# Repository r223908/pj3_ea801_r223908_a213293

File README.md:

### EA801 - PROJETO 3

### Câmbio CVT (v2) com BitDogLab V7

**Autores:** 
- Raul Galdino Tancredo (RA: 223908 / [@r223908](https://github.com/r223908))
- Arthur Lucas Da Silva Nogueira (RA: 213293 / [@arthurnog](https://github.com/arthurnog)))

**Professor:** Eric Rohmer

* **Proposta de projeto**: [Proposta em G-Docs](https://docs.google.com/document/d/12xUf4pp4VCcdJPwbZHKw6q6G0AQpYL8BC8JdEnKDbEA/edit?usp=sharing) (acesso "Comentador" para UNICAMP)
* **Relatório de projeto**: [Relatório em G-Docs](https://docs.google.com/document/d/11B9UFEimS15q4Ivua8mCu4cjH7NtBMuLyvma5xU35qU/edit?usp=sharing) (acesso "Comentador" para UNICAMP)
* **Demonstração do projeto no YouTube**: [Vídeo](https://youtube.com/shorts/MMiuudLj5G8)

---
## ⚙️ DESCRIÇÃO DO SISTEMA (v2)
O sistema desenvolvido consiste na implementação de uma bancada de testes para um **Câmbio de Transmissão Continuamente Variável (CVT)** simulado, controlado remotamente via interface sem fio. O projeto utiliza a plataforma BitDogLab V7 como unidade central de processamento, integrando comunicação serial, controle de potência e telemetria. O controle é dividido em dois eixos de atuação:
1. Eixo motor: Um motor de corrente contínua (DC), simulando a rotação do motor primário, controlado via PWM mas com a rotação travada em 100%.
2. Atuador do câmbio: Um segundo motor acoplado a um sistema de fuso (atuador linear), responsável por alterar a posição física da correia do câmbio CVT.

A interface homem-máquina (IHM) é realizada de forma remota através de um módulo Bluetooth (conectado à interface UART da placa) com a integração de um aplicativo no celular. O display OLED da placa é utilizado para exibir a telemetria em tempo real.

A realimentação da posição do atuador do CVT é realizada por meio de um sensor de distância óptico Time of Flight (ToF) VL6180X. Cabe ressaltar que o atual protótipo apresenta diversas otimizações mecânicas e elétricas em relação ao projeto original desenvolvido na etapa anterior da disciplina (PJ2).

<figure align="center">
    <figcaption><i>Diagrama de blocos do projeto.</i></figcaption>
    
    </br>
</figure>

<figure align="center">
    <figcaption>
        <i>Projeto em CAD 3D (PJ3).
        <br>PDF 3D (abrir com Foxit ou Adobe): <a href="https://github.com/r223908/pj3_ea801_r223908_a213293/blob/main/docs/6_CAD-files/ea801_pj3_cvt_pdf3D.PDF">/docs/6_CAD-files/ea801_pj3_cvt_pdf3D</a></i></i>
    </figcaption>
    <table align="center">
    <tr>
    <td align="center">
        <br>
    </td>
    <td align="center">
        <br>
    </td>
    </tr>
</table>
</figure>

<figure align="center">
    <figcaption>
        <i>Equipamento montado #1 (PJ3).</i>
    </figcaption>
    <table align="center">
    <tr>
    <td align="center">
        <br>
    </td>
    <td align="center">
        <br>
    </td>
    </tr>
</table>
</figure>

<figure align="center">
    <figcaption>
        <i>Equipamento montado #2 (PJ3).</i>
    </figcaption>
    <table align="center">
    <tr>
    <td align="center">
        <br>
    </td>
    <td align="center">
        <br>
    </td>
    </tr>
</table>
</figure>

<figure align="center">
    <figcaption><i>Equipamento montado #3 (PJ3).</i></figcaption>
    
    </br>
</figure>

---
## ❗REQUISITOS
- 1x BitDogLab V7.
- 2x motores DC com caixa de redução
- 2x capacitores cerâmicos 100 nF (cód.: 104)
- 1x Ponte H L293D (CI) para ambos os motores.
- 1x Sensor ToF VL6180X
- Placa de fenolite para a shield da BitDogLab
- Jumpers M-M e M-F.
- 3x pilhas 18650: 2x para os motores e 1x para a placa
- *Case* com cabos para 2 pilhas 18650 em paralelo.
- Cabo micro USB (usar apenas para passar a programação, com as pilhas desconectadas).
- Módulo Bluetooth HC-05.
- Anel o-ring ou elástico para o câmbio.
- Elementos de fixação
    - 1x Parafuso ISO 4017 M6x15 (Contra-eixo do cone principal)
    - 1x Parafuso ISO 4017 M6x60 (fuso do CVT)
    - 2x Porca ISO 4032 M6 (Espaçador no fuso do CVT e guia da polia)
    - 1x Arruela ISO 7093 Ø6 (Espaçador no fuso do CVT)
    - 4x Parafuso auto atarrachante 9/64"x1" (ou 1/8"x1" - Ø x Comprimento)
- Peças impressas em 3D
- Ambiente de desenvolvimento configurado para MicroPython.

---
## 🔧CONFIGURAÇÕES
- BitDogLab V7: Transferir os arquivos **main.py**, **setup.py**, **vl6180x.py** e **ssd1306.py** para a placa via USB.
- Ligação das pontes H e motores conforme **/docs/images/schematic_pj3.png**
- Módulo Bluetooth HC05 configurado com AT Mode usando **hc05_atMode_config.py**
- Sensor VL6180X calibrado conforme **/libs/tools/vl6180x_calibrate**

---
## 📚 REFERÊNCIAS
1. Repositório BitDogLab V7: [Repositório no GitHub](https://gitlab.unicamp.br/fabiano/bitdoglab-v7)
2. Banco de Informação de Hardware: [BitDogLabV7_BIH](https://docs.google.com/document/d/13-68OqiU7ISE8U2KPRUXT2ISeBl3WPhXjGDFH52eWlU/edit?tab=t.0)
3. LEGO Continuous Variable Transmission (CVT) V3 [Link YouTube](https://www.youtube.com/watch?v=sa60egMprYc)
4. LEGO Simple CVT (Continuously Variable Transmission) [Link YouTube](https://www.youtube.com/watch?v=1y5fQr0dDVg)
5. Time-of-Flight (ToF) proximity sensor and ambient light sensing (ALS) module [VL6180X](https://www.st.com/en/imaging-and-photonics-solutions/vl6180x.html)
6. Using one or more VL6180X 20cm Time-of-Flight proximity sensor with Arduino [Link YouTube](https://www.youtube.com/watch?v=_H9D0czQpSI)

---
## 📄LICENÇA
* Ver o arquivo `LICENSE`.

---
## 📂 ESTRUTURA DO PROJETO
``` text
├── .vscode/                        → Configurações para o ambiente de trabalho no VSCode
├── docs/                           → Documentação do projeto
│   ├── 1_folhas-de-dados/          → Folhas de dados dos equipamentos utilizados
│   ├── 2_images/                   → Imagens para relatórios e referências
│   ├── 3_mermaid-files/            → arquivos para gerar os diagramas de bloco e gantt
│   ├── 4_kicad-pj3/                → Projeto KiCad para a plaquinha shield
│   ├── 5_video/                    → Vídeo do equipamento em operação
│   ├── 6_CAD-files/                → Arquivos .stl e PDF_3D da montagem
│   └── (...)                       → Proposta e relatório
├── libs/
│   ├── tools/                      → Códigos para configuração dos equipamentos                           
│   └── (...)                       → Bibliotecas
├── src/                            
│   └── main.py                     → Código-fonte
├── .micropico                      → Arquivo necessário para a extensão Pi PICO no VSCODE
├── LICENSE                         → Licença de uso do código
└── README.md                       → Resumo e estrutura do projeto
```

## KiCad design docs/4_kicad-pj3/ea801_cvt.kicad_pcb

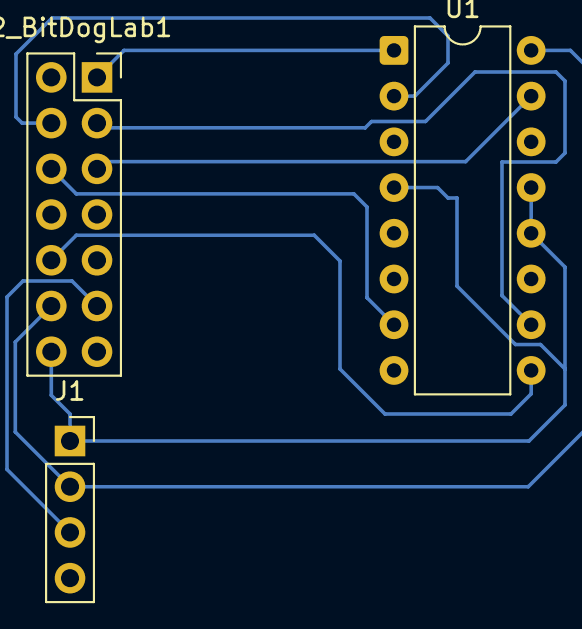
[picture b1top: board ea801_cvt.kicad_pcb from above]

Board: 2 copper layers, 3 parts (0 on the bottom side), 10 nets.

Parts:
J1: Conn_01x04; PinSocket_1x04_P2.54mm_Vertical
J2_BitDogLab1: J2_IDC_BitDogLab; PinSocket_2x07_P2.54mm_Vertical
U1: L293D; DIP-16_W7.62mm

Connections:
/3V3: J1.2, J2_BitDogLab1.3V3 (Pin_2), U1.16 (VCC1)
/GP8: J1.SDA, J2_BitDogLab1.GP8 (Pin_13)
/GP9: J1.SCL, J2_BitDogLab1.GP9 (Pin_12)
/GP16: J2_BitDogLab1.GP16 (Pin_6), U1.2 (1A)
/GP17: J2_BitDogLab1.GP17 (Pin_5), U1.7 (2A)
/GP19: J2_BitDogLab1.GP19 (Pin_9), U1.10 (3A)
/GP20: J2_BitDogLab1.GP20 (Pin_10), U1.15 (4A)
/GP28: J2_BitDogLab1.GP28 (Pin_3), U1.9 (EN3,4)
GND: J1.1, J2_BitDogLab1.GND (Pin_1), U1.4 (GND), U1.5 (GND), U1.12 (GND), U1.13 (GND)
unnamed: J2_BitDogLab1.GP18 (Pin_8), U1.1 (EN1,2)

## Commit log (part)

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2026-04-29 commit inicial
2026-04-29 colocando arquivos do pj2
2026-04-30 datasheets, readme criado e preenchido, arquivos mermaid inicializados
2026-05-01 upload do projeto novo do kicad
2026-05-01 att gitignore
2026-05-01 placholder for empty folders
2026-05-04 datasheet do ToF e testes
2026-05-05 att readme, inclusão imagens e diagrama de blocos do sistema
2026-05-05 att imagem do diagrama de blocos e teste com escalas das imagens no readme; att readme no link do pdf 3D
2026-05-05 teste 2 com as imagens do readme
2026-05-05 renomeando a pasta 1_datasheets para 1_folha-de-dados, att readme e inc imagem do gantt do pj3
2026-05-05 inclusão link do relatório (in-work) no readme
2026-05-05 upload arquivo preliminar da proposta
2026-05-18 upload arquivos .stl
2026-05-23 revisao de alguns pontos e inicio dos testes com 3D
2026-05-24 inc imagens, att projeto kicad e att dos arquivos do sensor ToF
2026-06-08 import setup.py and main.py from previous project
2026-06-08 upload of functioning l293d config and ToF reading; toDO: ToF control of CVT motor
2026-06-14 commit da versão que funcionou tudo
2026-06-27 finalizacao dos testes
2026-06-27 asbuilt do projeto do schematic
2026-06-27 trash files from kicad
2026-06-28 att readme and upload images
2026-06-28 att images folder
2026-06-28 new image for the report
2026-06-28 upload video and update link in readme
2026-06-28 upload the report .pdf
2026-06-28 updated image paths in readme
2026-06-28 update image captions in readme
2026-06-28 att readme
